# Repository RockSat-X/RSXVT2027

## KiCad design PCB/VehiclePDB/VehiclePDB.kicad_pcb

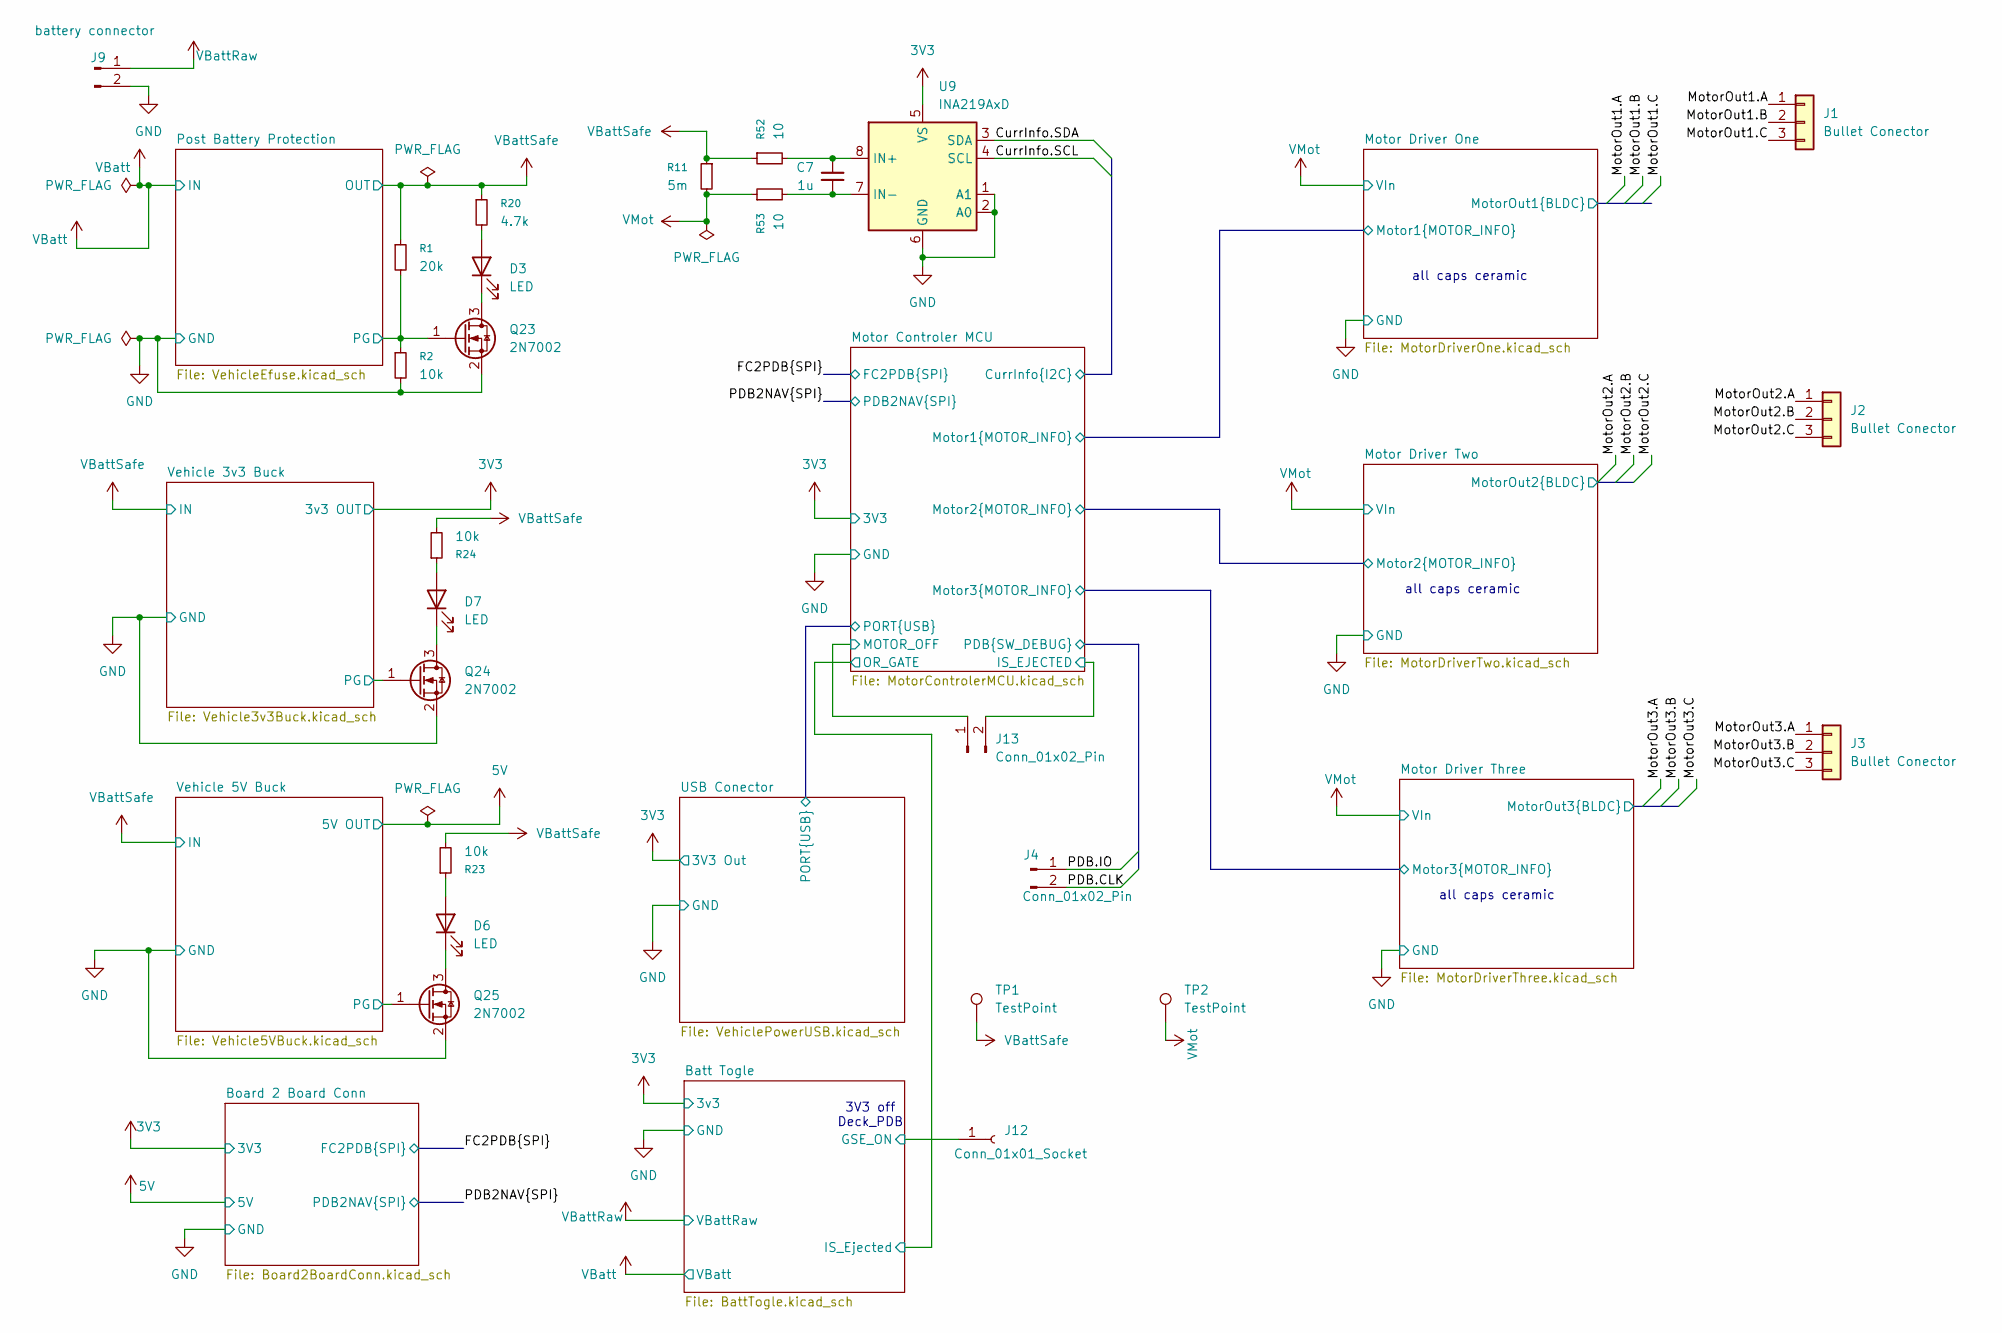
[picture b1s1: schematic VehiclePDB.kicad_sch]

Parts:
C7: 1u; C_0402_1005Metric
D3, D6, D7: LED; LED_0402_1005Metric
J1, J2, J3: Bullet Conector; AMASS_MR30PW-M_1x03_P3.50mm_Horizontal
J4: Conn_01x02_Pin; PinHeader_1x02_P2.54mm_Vertical
J9: battery connector; AMASS_XT30PW-M_1x02_P2.50mm_Horizontal
J12: Conn_01x01_Socket; PinSocket_1x01_P2.00mm_Vertical
J13: Conn_01x02_Pin; JST_PH_B2B-PH-K_1x02_P2.00mm_Vertical
Q23, Q24, Q25: 2N7002; SOT-23
R1: 20k; R_0402_1005Metric
R2, R23, R24: 10k; R_0402_1005Metric
R11: 5m; R_Shunt_Vishay_WSR2_WSR3
R20: 4.7k; R_0402_1005Metric
R52, R53: 10; R_0402_1005Metric
TP1, TP2: TestPoint; TestPoint_Bridge_Pitch2.0mm_Drill0.7mm
U9: INA219AxD; SOIC-8_3.9x4.9mm_P1.27mm

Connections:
3V3: U9.5 (VS); also elsewhere on the board
/Batt Togle/GSE_ON: J12.1 (Pin_1_1); also elsewhere on the board
/Motor Controler MCU/CurrInfo.SCL: U9.4 (SCL); also elsewhere on the board
/Motor Controler MCU/CurrInfo.SDA: U9.3 (SDA); also elsewhere on the board
/Motor Controler MCU/IS_EJECTED: J13.2; also elsewhere on the board
/Motor Controler MCU/MOTOR_OFF: J13.1; also elsewhere on the board
/Motor Controler MCU/PDB.CLK: J4.2; also elsewhere on the board
/Motor Controler MCU/PDB.IO: J4.1; also elsewhere on the board
/Motor Driver One/U.Switch: J1.3; also elsewhere on the board
/Motor Driver One/V.Switch: J1.2; also elsewhere on the board
/Motor Driver One/W.Switch: J1.1; also elsewhere on the board
/Motor Driver Three/U.Switch: J3.3; also elsewhere on the board
/Motor Driver Three/V.Switch: J3.2; also elsewhere on the board
/Motor Driver Three/W.Switch: J3.1; also elsewhere on the board
/Motor Driver Two/U.Switch: J2.3; also elsewhere on the board
/Motor Driver Two/V.Switch: J2.2; also elsewhere on the board
/Motor Driver Two/W.Switch: J2.1; also elsewhere on the board
/Post Battery Protection/PG: Q23.1 (G), R1.2, R2.1; also elsewhere on the board
/Vehicle 3v3 Buck/PG: Q24.1 (G); also elsewhere on the board
/Vehicle 5V Buck/PG: Q25.1 (G); also elsewhere on the board
unnamed: D3.2 (A), R20.2
unnamed: D3.1 (K), Q23.3 (D)
unnamed: D6.2 (A), R23.1
unnamed: D6.1 (K), Q25.3 (D)
unnamed: D7.2 (A), R24.1
unnamed: D7.1 (K), Q24.3 (D)
unnamed: C7.1, R52.2, U9.8 (IN+)
unnamed: C7.2, R53.2, U9.7 (IN-)
VBattRaw: J9.1; also elsewhere on the board
VBattSafe: R1.1, R11.1, R20.1, R23.2, R24.2, R52.1, TP1.1 (1_1); also elsewhere on the board
VMot: R11.2, R53.1, TP2.1 (1_1); also elsewhere on the board

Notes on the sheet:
3V3 off Deck_PDB
all caps ceramic

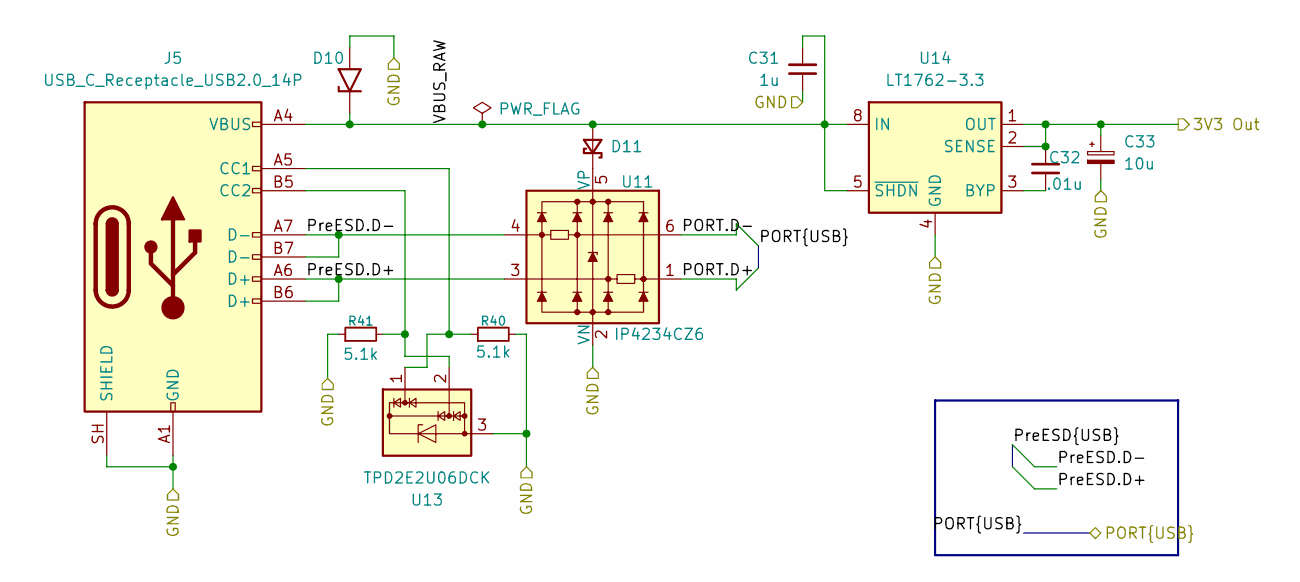
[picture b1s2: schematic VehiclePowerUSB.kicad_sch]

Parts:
C31: 1u; C_0402_1005Metric
C32: .01u; C_0402_1005Metric
C33: 10u; C_0402_1005Metric
D10: SMBJ6.0A-E3/52; D_SMB
D11: BAT54; TSOT-23
J5: USB_C_Receptacle_USB2.0_14P; USB_C_Receptacle_GCT_USB4105-xx-A_16P_TopMnt_Horizontal
R40, R41: 5.1k; R_0402_1005Metric
U11: IP4234CZ6; SC-74-6_1.55x2.9mm_P0.95mm
U13: TPD2E2U06DCK; SOT-323_SC-70
U14: LT1762-3.3; MSOP-8_3x3mm_P0.65mm

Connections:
3V3: C32.1, C33.1, U14.1 (OUT), U14.2 (SENSE); also elsewhere on the board
/USB Conector/PORT.D+: U11.1; also elsewhere on the board
/USB Conector/PORT.D-: U11.6; also elsewhere on the board
/USB Conector/PreESD.D+: J5.A6 (D+), J5.B6 (D+), U11.3
/USB Conector/PreESD.D-: J5.A7 (D-), J5.B7 (D-), U11.4
/USB Conector/VBUS_RAW: C31.1, D10.1 (A1), D11.1 (A), J5.A4 (VBUS), J5.A9 (VBUS), J5.B4 (VBUS), J5.B9 (VBUS), U14.5 (~SHDN), U14.8 (IN)
unnamed: D11.3 (K), U11.5 (VP)
unnamed: J5.A5 (CC1), R40.1, U13.1
unnamed: J5.B5 (CC2), R41.2, U13.2
unnamed: C32.2, U14.3 (BYP)

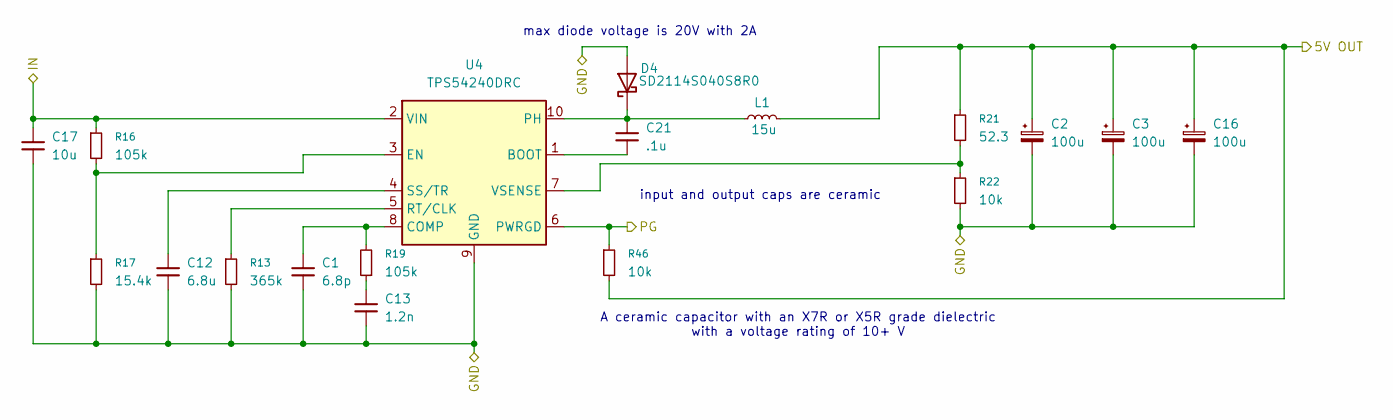
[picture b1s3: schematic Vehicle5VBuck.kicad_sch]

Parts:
C1: 6.8p; C_0402_1005Metric
C2, C3, C16: 100u; C_0402_1005Metric
C12: 6.8u; C_0402_1005Metric
C13: 1.2n; C_0402_1005Metric
C17: 10u; C_0402_1005Metric
C21: .1u; C_0402_1005Metric
D4: SD2114S040S8R0; D_2114_3652Metric
L1: 15u; L_Wurth_WE-LQS-8040
R13: 365k; R_0402_1005Metric
R16, R19: 105k; R_0402_1005Metric
R17: 15.4k; R_0402_1005Metric
R21: 52.3; R_0402_1005Metric
R22, R46: 10k; R_0402_1005Metric
U4: TPS54240DRC; Texas_DRC0010J_ThermalVias

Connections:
5V: C2.1, C3.1, C16.1, L1.2, R21.1, R46.2; also elsewhere on the board
/Vehicle 5V Buck/PG: R46.1, U4.6 (PWRGD); also elsewhere on the board
unnamed: C13.2, R19.1
unnamed: C21.1, D4.1 (K), L1.1, U4.10 (PH)
unnamed: C21.2, U4.1 (BOOT)
unnamed: C1.1, R19.2, U4.8 (COMP)
unnamed: R16.2, R17.1, U4.3 (EN)
unnamed: R13.1, U4.5 (RT/CLK)
unnamed: C12.1, U4.4 (SS/TR)
unnamed: R21.2, R22.1, U4.7 (VSENSE)
VBattSafe: C17.1, R16.1, U4.2 (VIN); also elsewhere on the board

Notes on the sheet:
A ceramic capacitor with an X7R or X5R grade dielectric with a voltage rating of 10+ V
input and output caps are ceramic
max diode voltage is 20V with 2A

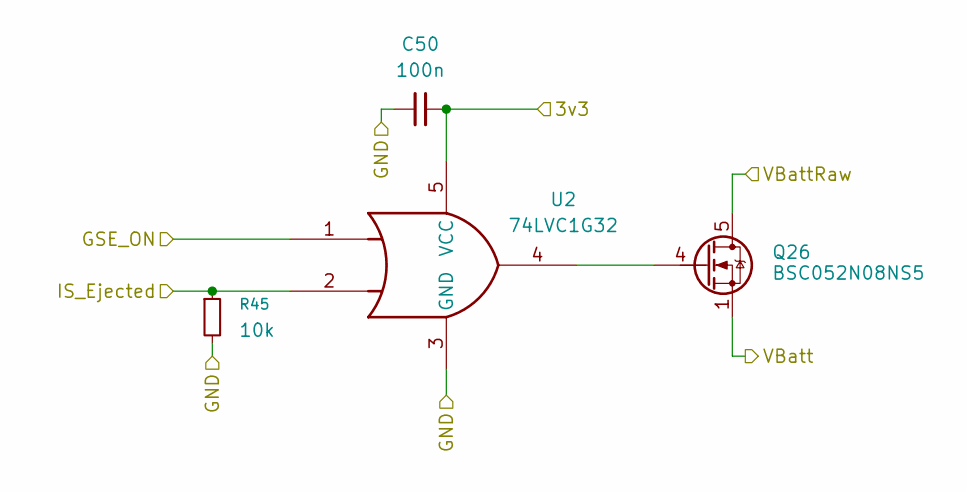
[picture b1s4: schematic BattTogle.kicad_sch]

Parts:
C50: 100n; C_0402_1005Metric
Q26: BSC052N08NS5; TDSON-8-1
R45: 10k; R_0402_1005Metric_Pad0.72x0.64mm_HandSolder
U2: 74LVC1G32; SOT-23-5

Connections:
3V3: C50.2, U2.5 (VCC); also elsewhere on the board
/Batt Togle/GSE_ON: U2.1; also elsewhere on the board
unnamed: Q26.4 (G), U2.4
VBatt: Q26.1 (S), Q26.2 (S), Q26.3 (S); also elsewhere on the board
VBattRaw: Q26.5 (D); also elsewhere on the board

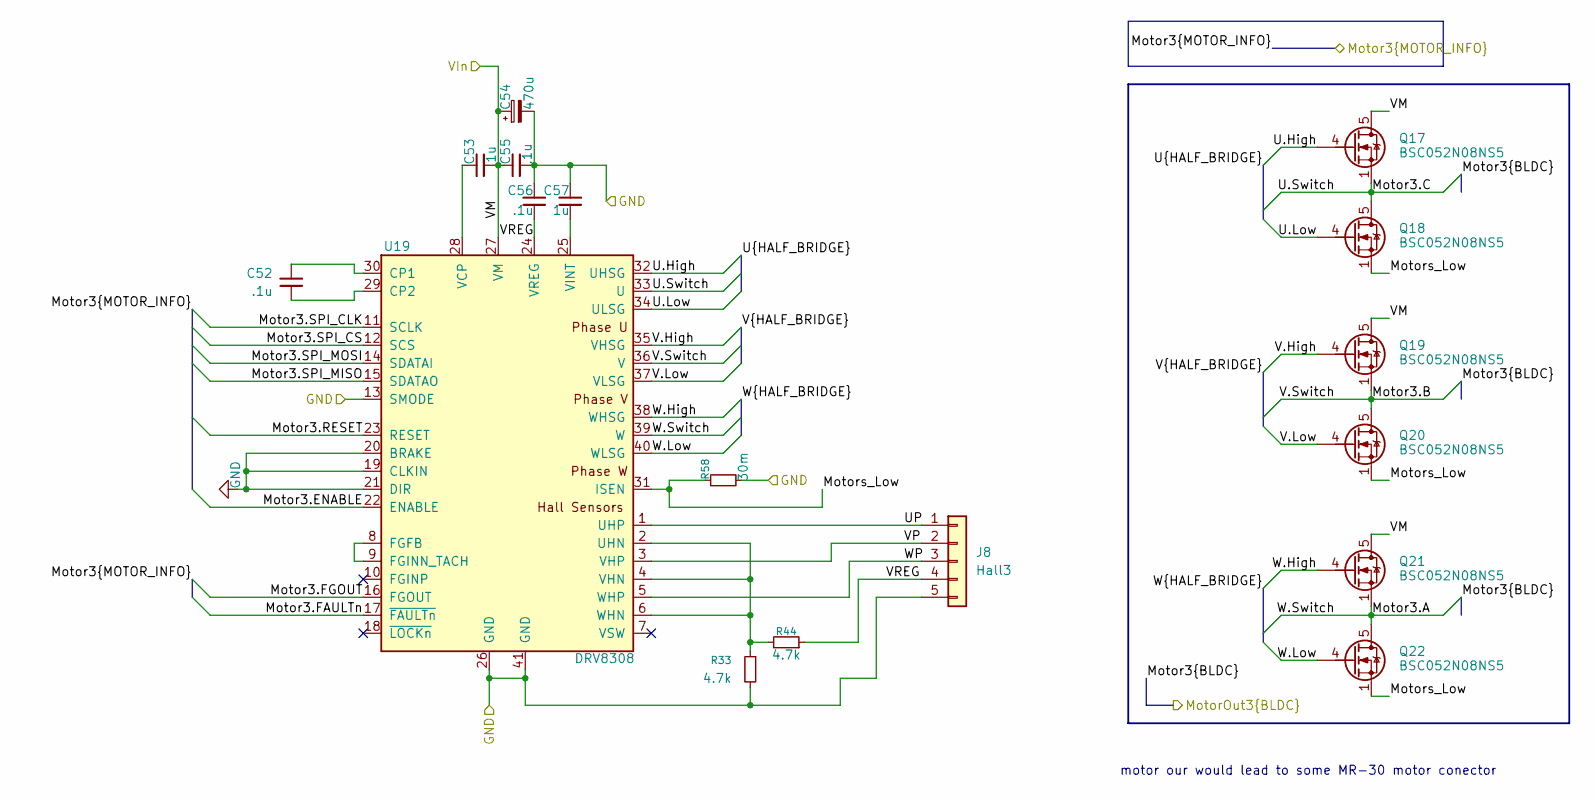
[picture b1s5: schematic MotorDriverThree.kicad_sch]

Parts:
C52, C55, C56: .1u; C_0402_1005Metric
C53, C57: 1u; C_0402_1005Metric
C54: 470u; C_0402_1005Metric
J8: Hall3; JST_GH_SM05B-GHS-TB_1x05-1MP_P1.25mm_Horizontal
Q17, Q18, Q19, Q20, Q21, Q22: BSC052N08NS5; TDSON-8-1
R33, R44: 4.7k; R_0402_1005Metric
R58: 30m; R_Shunt_Vishay_WSR2_WSR3
U19: DRV8308; Texas_RHA0040E_VQFN-40-1EP_6x6mm_P0.5mm_EP3.52x2.62mm

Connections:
/Motor Driver Three/Motor3.ENABLE: U19.22 (ENABLE); also elsewhere on the board
/Motor Driver Three/Motor3.FAULTn: U19.17 (~FAULTn); also elsewhere on the board
/Motor Driver Three/Motor3.FGOUT: U19.16 (FGOUT); also elsewhere on the board
/Motor Driver Three/Motor3.RESET: U19.23 (RESET); also elsewhere on the board
/Motor Driver Three/Motor3.SPI_CLK: U19.11 (SCLK); also elsewhere on the board
/Motor Driver Three/Motor3.SPI_CS: U19.12 (SCS); also elsewhere on the board
/Motor Driver Three/Motor3.SPI_MISO: U19.15 (SDATAO); also elsewhere on the board
/Motor Driver Three/Motor3.SPI_MOSI: U19.14 (SDATAI); also elsewhere on the board
/Motor Driver Three/Motors_Low: Q18.1 (S), Q18.2 (S), Q18.3 (S), Q20.1 (S), Q20.2 (S), Q20.3 (S), Q22.1 (S), Q22.2 (S), Q22.3 (S), R58.1, U19.31 (ISEN)
/Motor Driver Three/U.High: Q17.4 (G), U19.32 (UHSG)
/Motor Driver Three/U.Low: Q18.4 (G), U19.34 (ULSG)
/Motor Driver Three/U.Switch: Q17.1 (S), Q17.2 (S), Q17.3 (S), Q18.5 (D), U19.33 (U); also elsewhere on the board
/Motor Driver Three/UP: J8.1, U19.1 (UHP)
/Motor Driver Three/V.High: Q19.4 (G), U19.35 (VHSG)
/Motor Driver Three/V.Low: Q20.4 (G), U19.37 (VLSG)
/Motor Driver Three/V.Switch: Q19.1 (S), Q19.2 (S), Q19.3 (S), Q20.5 (D), U19.36 (V); also elsewhere on the board
/Motor Driver Three/VP: J8.2, U19.3 (VHP)
/Motor Driver Three/W.High: Q21.4 (G), U19.38 (WHSG)
/Motor Driver Three/W.Low: Q22.4 (G), U19.40 (WLSG)
/Motor Driver Three/W.Switch: Q21.1 (S), Q21.2 (S), Q21.3 (S), Q22.5 (D), U19.39 (W); also elsewhere on the board
/Motor Driver Three/WP: J8.3, U19.5 (WHP)
unnamed: C52.1, U19.30 (CP1)
unnamed: C52.2, U19.29 (CP2)
unnamed: U19.8 (FGFB), U19.9 (FGINN_TACH)
unnamed: C53.1, U19.28 (VCP)
unnamed: C57.2, U19.25 (VINT)
VMot: C53.2, C54.1, C55.1, Q17.5 (D), Q19.5 (D), Q21.5 (D), U19.27 (VM); also elsewhere on the board

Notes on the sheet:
motor our would lead to some MR-30 motor conector

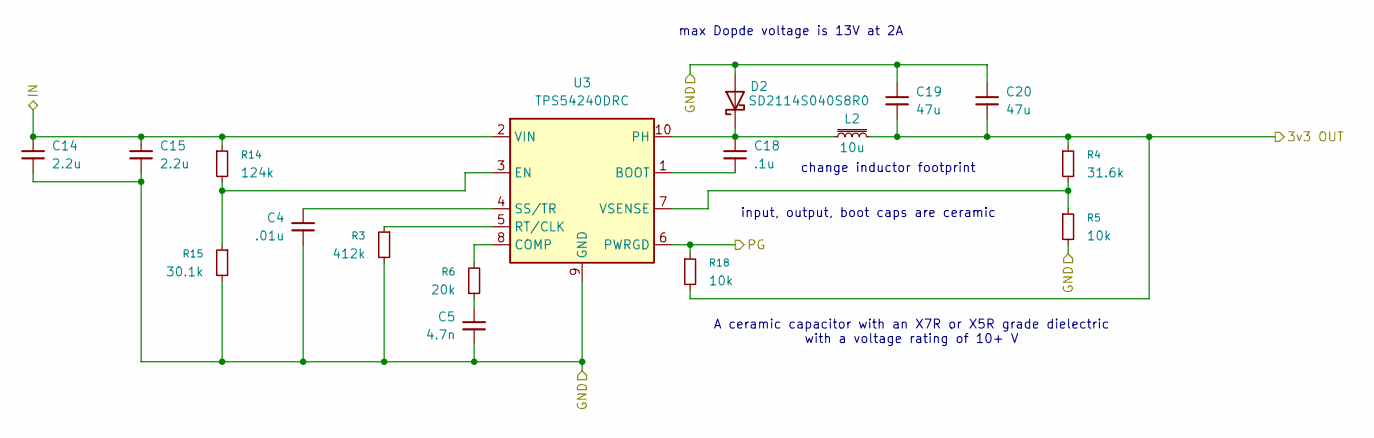
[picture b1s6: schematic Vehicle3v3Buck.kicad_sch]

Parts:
C4: .01u; C_0402_1005Metric
C5: 4.7n; C_0402_1005Metric
C14, C15: 2.2u; C_0402_1005Metric
C18: .1u; C_0402_1005Metric
C19, C20: 47u; C_0402_1005Metric
D2: SD2114S040S8R0; D_2114_3652Metric
L2: 10u; L_Wurth_WE-LQS-8040
R3: 412k; R_0402_1005Metric
R4: 31.6k; R_0402_1005Metric
R5, R18: 10k; R_0402_1005Metric
R6: 20k; R_0402_1005Metric
R14: 124k; R_0402_1005Metric
R15: 30.1k; R_0402_1005Metric
U3: TPS54240DRC; Texas_DRC0010J_ThermalVias

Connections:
3V3: C19.2, C20.2, L2.2, R4.1, R18.2; also elsewhere on the board
/Vehicle 3v3 Buck/PG: R18.1, U3.6 (PWRGD); also elsewhere on the board
unnamed: C5.2, R6.1
unnamed: C18.1, D2.1 (K), L2.1, U3.10 (PH)
unnamed: C18.2, U3.1 (BOOT)
unnamed: R6.2, U3.8 (COMP)
unnamed: R14.2, R15.1, U3.3 (EN)
unnamed: R3.1, U3.5 (RT/CLK)
unnamed: C4.1, U3.4 (SS/TR)
unnamed: R4.2, R5.1, U3.7 (VSENSE)
VBattSafe: C14.1, C15.1, R14.1, U3.2 (VIN); also elsewhere on the board

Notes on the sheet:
input, output, boot caps are ceramic
change inductor footprint
A ceramic capacitor with an X7R or X5R grade dielectric with a voltage rating of 10+ V
max Dopde voltage is 13V at 2A

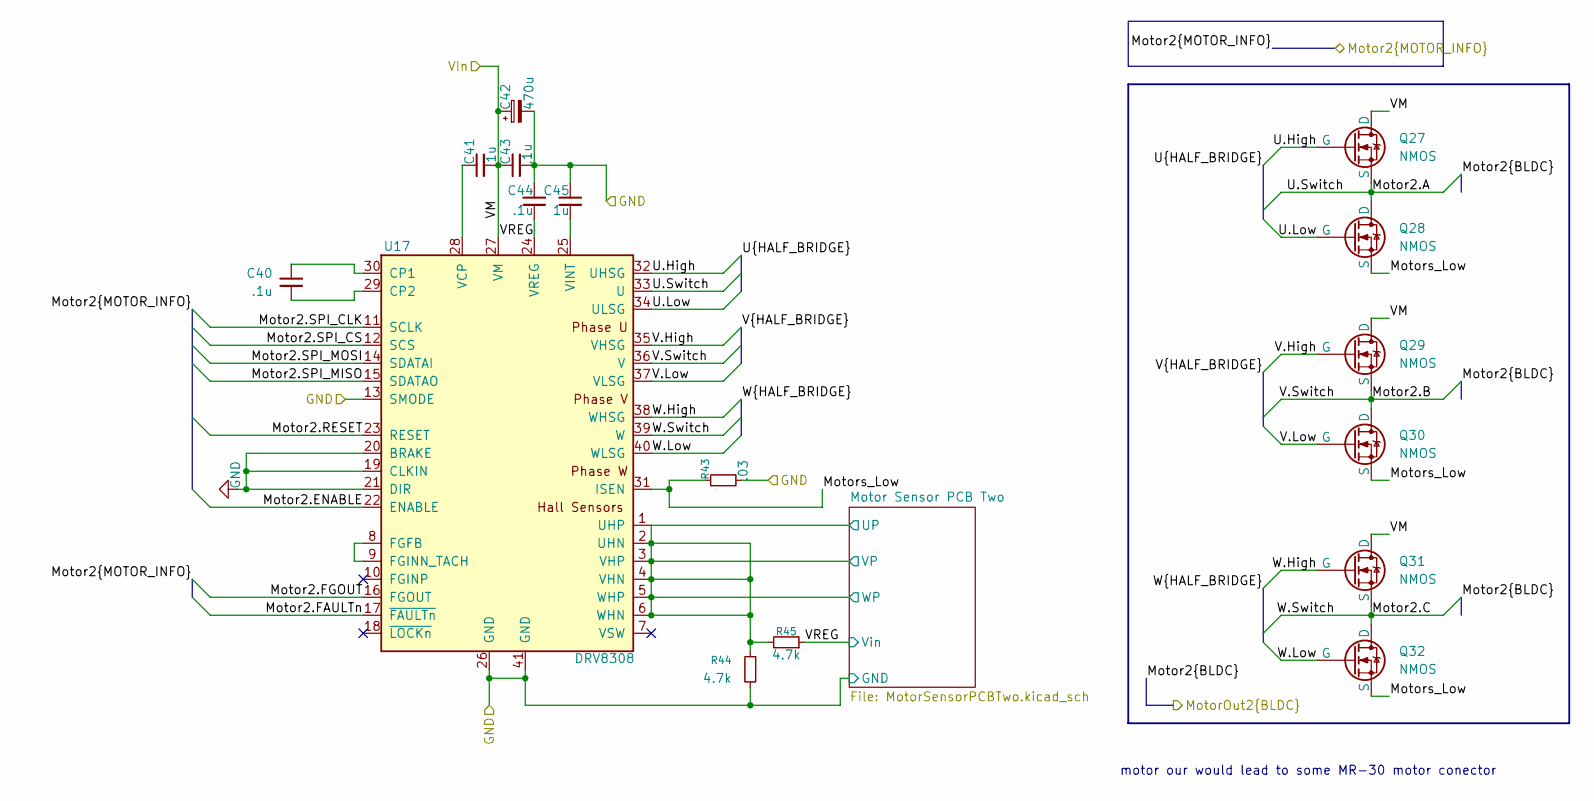
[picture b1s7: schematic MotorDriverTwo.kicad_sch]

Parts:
C40, C43, C44: .1u; C_0402_1005Metric
C41, C45: 1u; C_0402_1005Metric
C42: 470u; C_0402_1005Metric
Q27, Q28, Q29, Q30, Q31, Q32: NMOS
R43: .03; R_0402_1005Metric
R44, R45: 4.7k; R_0402_1005Metric
U17: DRV8308; Texas_RHA0040E_VQFN-40-1EP_6x6mm_P0.5mm_EP3.52x2.62mm

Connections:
/Motor Driver Three/Motor3.RESET: U17.23 (RESET); also elsewhere on the board
/Motor Driver Three/Motor3.SPI_CLK: U17.11 (SCLK); also elsewhere on the board
/Motor Driver Three/Motor3.SPI_MISO: U17.15 (SDATAO); also elsewhere on the board
/Motor Driver Three/Motor3.SPI_MOSI: U17.14 (SDATAI); also elsewhere on the board
/Motor Driver Two/Motor2.ENABLE: U17.22 (ENABLE); also elsewhere on the board
/Motor Driver Two/Motor2.FAULTn: U17.17 (~FAULTn); also elsewhere on the board
/Motor Driver Two/Motor2.FGOUT: U17.16 (FGOUT); also elsewhere on the board
/Motor Driver Two/Motor2.SPI_CS: U17.12 (SCS); also elsewhere on the board
/Motor Driver Two/Motors_Low: Q28.3 (S), Q30.3 (S), Q32.3 (S), R43.1, U17.31 (ISEN); also elsewhere on the board
/Motor Driver Two/U.High: Q27.2 (G), U17.32 (UHSG); also elsewhere on the board
/Motor Driver Two/U.Low: Q28.2 (G), U17.34 (ULSG); also elsewhere on the board
/Motor Driver Two/U.Switch: Q27.3 (S), Q28.1 (D), U17.33 (U); also elsewhere on the board
/Motor Driver Two/V.High: Q29.2 (G), U17.35 (VHSG); also elsewhere on the board
/Motor Driver Two/V.Low: Q30.2 (G), U17.37 (VLSG); also elsewhere on the board
/Motor Driver Two/V.Switch: Q29.3 (S), Q30.1 (D), U17.36 (V); also elsewhere on the board
/Motor Driver Two/W.High: Q31.2 (G), U17.38 (WHSG); also elsewhere on the board
/Motor Driver Two/W.Low: Q32.2 (G), U17.40 (WLSG); also elsewhere on the board
/Motor Driver Two/W.Switch: Q31.3 (S), Q32.1 (D), U17.39 (W); also elsewhere on the board
unnamed: C40.1, U17.30 (CP1)
unnamed: C40.2, U17.29 (CP2)
unnamed: U17.8 (FGFB), U17.9 (FGINN_TACH)
unnamed: C41.1, U17.28 (VCP)
unnamed: C45.2, U17.25 (VINT)
VMot: C41.2, C42.1, C43.1, Q27.1 (D), Q29.1 (D), Q31.1 (D), U17.27 (VM); also elsewhere on the board

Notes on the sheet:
motor our would lead to some MR-30 motor conector

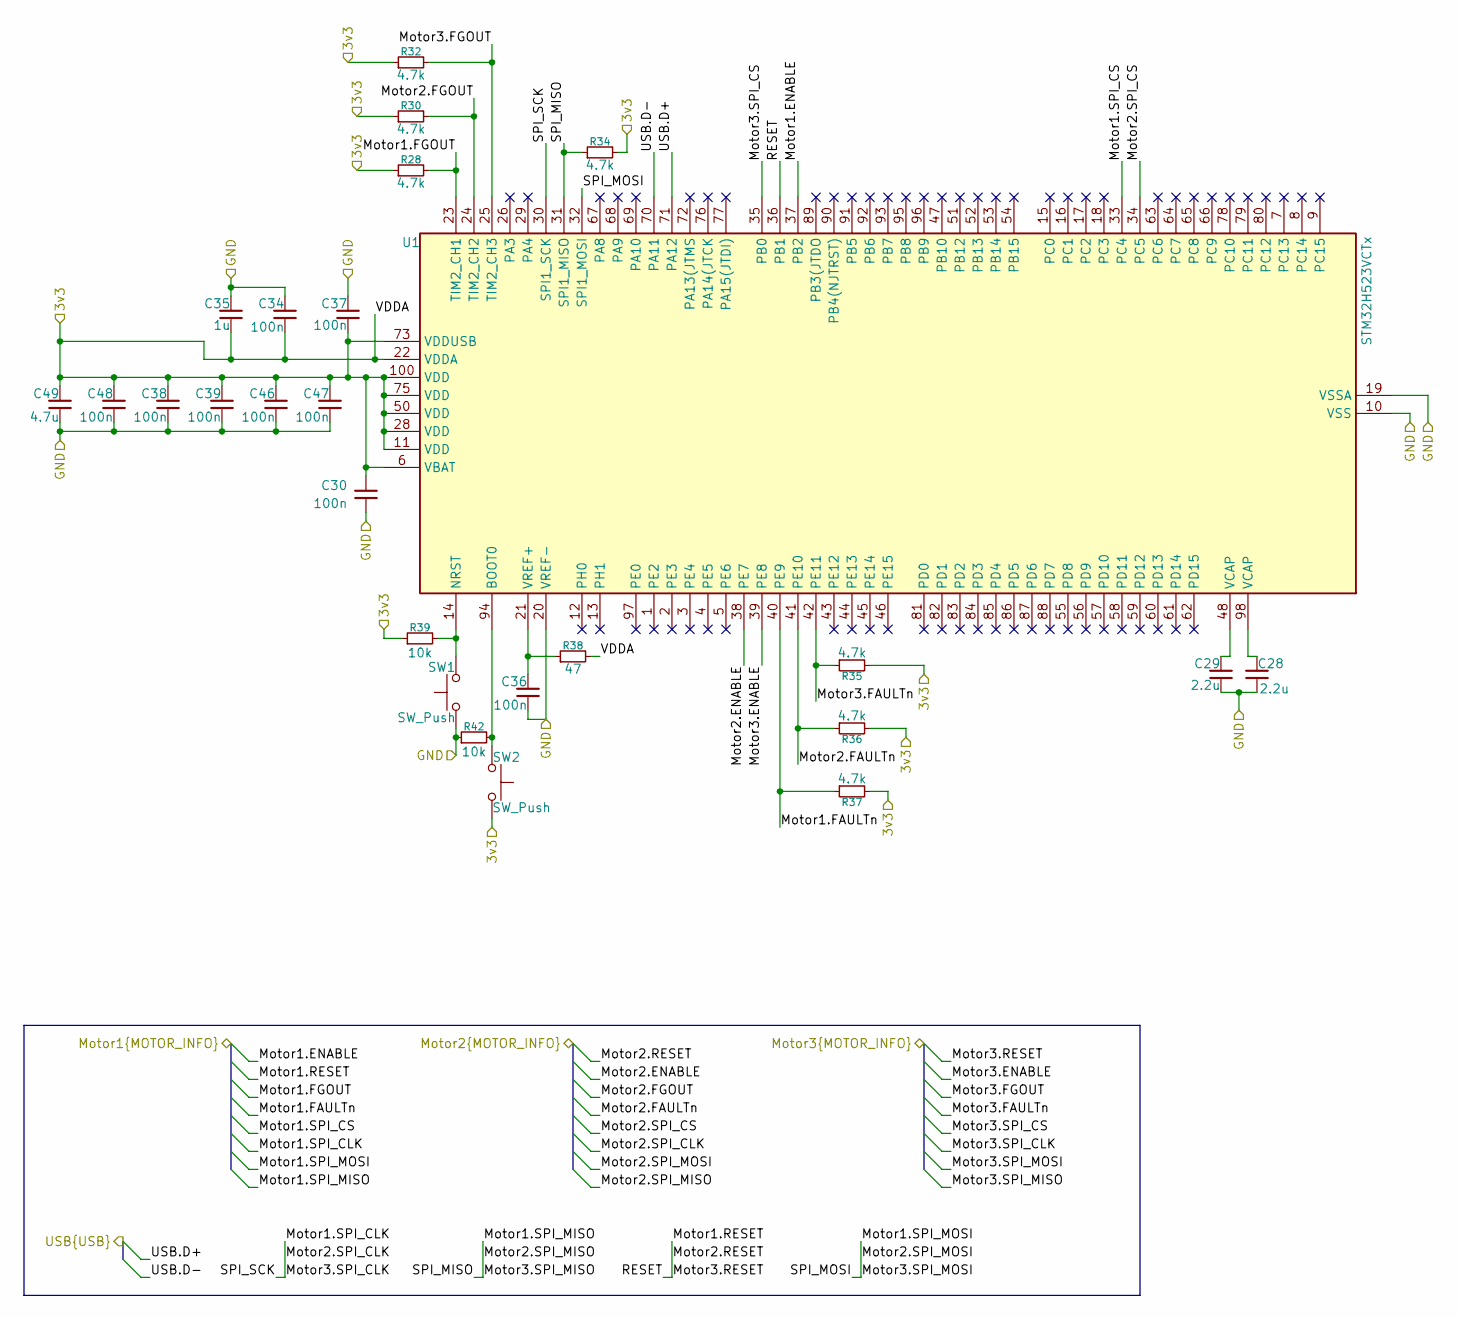
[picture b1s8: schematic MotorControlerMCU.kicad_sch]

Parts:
C28, C29: 2.2u; C_0402_1005Metric
C30, C34, C36, C37, C38, C39, C46, C47, C48: 100n; C_0402_1005Metric
C35: 1u; C_0402_1005Metric
C49: 4.7u; C_0402_1005Metric
R28, R30, R32, R34, R35, R36, R37: 4.7k; R_0402_1005Metric
R38: 47; R_0402_1005Metric
R39, R42: 10k; R_0402_1005Metric
SW1, SW2: SW_Push; SW_Push_1P1T_NO_CK_KMR2
U1: STM32H523VCTx; LQFP-100_14x14mm_P0.5mm

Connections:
3V3: C30.1, C34.2, C35.2, C37.1, C38.1, C39.1, C46.1, C47.1, C48.1, C49.1, R28.1, R30.1, R32.1, R34.2, R35.2, R36.2, R37.2, R38.2, R39.1, SW2.1, U1.6 (VBAT), U1.11 (VDD), U1.22 (VDDA), U1.28 (VDD), U1.50 (VDD), U1.73 (VDDUSB), U1.75 (VDD), U1.100 (VDD); also elsewhere on the board
/FC2PDB.CLK: U1.47 (SPI2_SCK); also elsewhere on the board
/FC2PDB.CS: U1.15 (PC0); also elsewhere on the board
/FC2PDB.MISO: U1.17 (SPI2_MISO); also elsewhere on the board
/FC2PDB.MOSI: U1.16 (SPI2_MOSI); also elsewhere on the board
/Motor Controler MCU/CurrInfo.SCL: U1.92 (I2C1_SCL); also elsewhere on the board
/Motor Controler MCU/CurrInfo.SDA: U1.93 (I2C1_SDA); also elsewhere on the board
/Motor Controler MCU/IS_EJECTED: U1.96 (PB9); also elsewhere on the board
/Motor Controler MCU/MOTOR_OFF: U1.97 (PE0); also elsewhere on the board
/Motor Controler MCU/PDB.CLK: U1.76 (DEBUG_JTCK-SWCLK); also elsewhere on the board
/Motor Controler MCU/PDB.IO: U1.72 (DEBUG_JTMS-SWDIO); also elsewhere on the board
/Motor Driver One/Motor1.ENABLE: U1.37 (PB2); also elsewhere on the board
/Motor Driver One/Motor1.FAULTn: R37.1, U1.40 (PE9); also elsewhere on the board
/Motor Driver One/Motor1.FGOUT: R28.2, U1.23 (TIM2_CH1); also elsewhere on the board
/Motor Driver One/Motor1.SPI_CS: U1.33 (PC4); also elsewhere on the board
/Motor Driver Three/Motor3.ENABLE: U1.39 (PE8); also elsewhere on the board
/Motor Driver Three/Motor3.FAULTn: R35.1, U1.42 (PE11); also elsewhere on the board
/Motor Driver Three/Motor3.FGOUT: R32.2, U1.25 (TIM2_CH3); also elsewhere on the board
/Motor Driver Three/Motor3.RESET: U1.36 (PB1); also elsewhere on the board
/Motor Driver Three/Motor3.SPI_CLK: U1.30 (SPI1_SCK); also elsewhere on the board
/Motor Driver Three/Motor3.SPI_CS: U1.35 (PB0); also elsewhere on the board
/Motor Driver Three/Motor3.SPI_MISO: R34.1, U1.31 (SPI1_MISO); also elsewhere on the board
/Motor Driver Three/Motor3.SPI_MOSI: U1.32 (SPI1_MOSI); also elsewhere on the board
/Motor Driver Two/Motor2.ENABLE: U1.38 (PE7); also elsewhere on the board
/Motor Driver Two/Motor2.FAULTn: R36.1, U1.41 (PE10); also elsewhere on the board
/Motor Driver Two/Motor2.FGOUT: R30.2, U1.24 (TIM2_CH2); also elsewhere on the board
/Motor Driver Two/Motor2.SPI_CS: U1.34 (PC5); also elsewhere on the board
/PDB2NAV.CLK: U1.1 (SPI4_SCK); also elsewhere on the board
/PDB2NAV.CS: U1.3 (PE4); also elsewhere on the board
/PDB2NAV.MISO: U1.4 (SPI4_MISO); also elsewhere on the board
/PDB2NAV.MOSI: U1.5 (SPI4_MOSI); also elsewhere on the board
/USB Conector/PORT.D+: U1.71 (USB_DP); also elsewhere on the board
/USB Conector/PORT.D-: U1.70 (USB_DM); also elsewhere on the board
unnamed: C28.1, U1.98 (VCAP)
unnamed: C29.1, U1.48 (VCAP)
unnamed: R42.2, SW2.2, U1.94 (BOOT0)
unnamed: R39.2, SW1.2, U1.14 (NRST)
unnamed: C36.1, R38.1, U1.21 (VREF+)

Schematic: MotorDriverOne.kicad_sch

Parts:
C22, C24, C26: .1u; C_0402_1005Metric
C23, C25: 1u; C_0402_1005Metric
C27: 470u; C_0402_1005Metric
J6: Hall1; JST_GH_SM05B-GHS-TB_1x05-1MP_P1.25mm_Horizontal
Q1, Q6, Q7, Q8, Q9, Q10: BSC052N08NS5; TDSON-8-1
R25: 30m; R_Shunt_Vishay_WSR2_WSR3
R26, R27: 4.7k; R_0402_1005Metric
U5: DRV8308; Texas_RHA0040E_VQFN-40-1EP_6x6mm_P0.5mm_EP3.52x2.62mm

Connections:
/Motor Driver One/Motor1.ENABLE: U5.22 (ENABLE); also elsewhere on the board
/Motor Driver One/Motor1.FAULTn: U5.17 (~FAULTn); also elsewhere on the board
/Motor Driver One/Motor1.FGOUT: U5.16 (FGOUT); also elsewhere on the board
/Motor Driver One/Motor1.SPI_CS: U5.12 (SCS); also elsewhere on the board
/Motor Driver One/Motors_Low: Q6.1 (S), Q6.2 (S), Q6.3 (S), Q7.1 (S), Q7.2 (S), Q7.3 (S), Q9.1 (S), Q9.2 (S), Q9.3 (S), R25.1, U5.31 (ISEN)
/Motor Driver One/U.High: Q1.4 (G), U5.32 (UHSG)
/Motor Driver One/U.Low: Q6.4 (G), U5.34 (ULSG)
/Motor Driver One/U.Switch: Q1.1 (S), Q1.2 (S), Q1.3 (S), Q6.5 (D), U5.33 (U); also elsewhere on the board
/Motor Driver One/UP: J6.1, U5.1 (UHP)
/Motor Driver One/V.High: Q8.4 (G), U5.35 (VHSG)
/Motor Driver One/V.Low: Q7.4 (G), U5.37 (VLSG)
/Motor Driver One/V.Switch: Q7.5 (D), Q8.1 (S), Q8.2 (S), Q8.3 (S), U5.36 (V); also elsewhere on the board
/Motor Driver One/VP: J6.2, U5.3 (VHP)
/Motor Driver One/VREG: C24.2, J6.4, R26.1, U5.24 (VREG)
/Motor Driver One/W.High: Q10.4 (G), U5.38 (WHSG)
/Motor Driver One/W.Low: Q9.4 (G), U5.40 (WLSG)
/Motor Driver One/W.Switch: Q9.5 (D), Q10.1 (S), Q10.2 (S), Q10.3 (S), U5.39 (W); also elsewhere on the board
/Motor Driver One/WP: J6.3, U5.5 (WHP)
/Motor Driver Three/Motor3.RESET: U5.23 (RESET); also elsewhere on the board
/Motor Driver Three/Motor3.SPI_CLK: U5.11 (SCLK); also elsewhere on the board
/Motor Driver Three/Motor3.SPI_MISO: U5.15 (SDATAO); also elsewhere on the board
/Motor Driver Three/Motor3.SPI_MOSI: U5.14 (SDATAI); also elsewhere on the board
unnamed: C22.1, U5.30 (CP1)
unnamed: C22.2, U5.29 (CP2)
unnamed: U5.8 (FGFB), U5.9 (FGINN_TACH)
unnamed: R26.2, R27.1, U5.2 (UHN), U5.4 (VHN), U5.6 (WHN)
unnamed: C23.1, U5.28 (VCP)
unnamed: C25.2, U5.25 (VINT)
VMot: C23.2, C26.1, C27.1, Q1.5 (D), Q8.5 (D), Q10.5 (D), U5.27 (VM); also elsewhere on the board

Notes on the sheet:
motor our would lead to some MR-30 motor conector

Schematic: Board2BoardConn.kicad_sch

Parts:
J10, J11: Conn_02x06_Odd_Even; JST_PHD_B12B-PHDSS_2x06_P2.00mm_Vertical

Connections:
3V3: J10.7, J10.8, J11.7, J11.8; also elsewhere on the board
5V: J10.9, J10.10, J11.9, J11.10; also elsewhere on the board
/FC2PDB.CLK: J10.4; also elsewhere on the board
/FC2PDB.CS: J10.1; also elsewhere on the board
/FC2PDB.MISO: J10.2; also elsewhere on the board
/FC2PDB.MOSI: J10.3; also elsewhere on the board
/PDB2NAV.CLK: J11.4; also elsewhere on the board
/PDB2NAV.CS: J11.1; also elsewhere on the board
/PDB2NAV.MISO: J11.2; also elsewhere on the board
/PDB2NAV.MOSI: J11.3; also elsewhere on the board

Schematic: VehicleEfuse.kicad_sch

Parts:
C6: .01u; C_0402_1005Metric
C8: 2.2n; C_0402_1005Metric
C9: 4.3n; C_0402_1005Metric
C10: 8.2n; C_0402_1005Metric
C11: 400u; C_0402_1005Metric
D1: SD2114S040S8R0; D_2114_3652Metric
D5: SMF15A; D_SMF
Q5: BSC026N08NS5; TDSON-8-1
R7: 500k; R_0402_1005Metric
R8: 14k; R_0402_1005Metric
R9: 50k; R_0402_1005Metric
R10: 226; R_0402_1005Metric
R12: 1.24k; R_0402_1005Metric
R47: 2; R_0402_1005Metric
U6: TPS25983

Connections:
/Post Battery Protection/PG: U6.13 (PG); also elsewhere on the board
unnamed: Q5.4 (G), R47.1
unnamed: Q5.1 (S), Q5.2 (S), Q5.3 (S), U6.17 (OUT), U6.18 (OUT), U6.19 (OUT), U6.20 (OUT), U6.21 (OUT), U6.22 (OUT), U6.23 (OUT), U6.24 (OUT)
unnamed: R7.1, R8.2, U6.6 (EN/UVLO)
unnamed: R10.1, U6.8 (ILIM)
unnamed: R12.1, U6.9 (IMON)
unnamed: C9.1, U6.7 (ITIMER)
unnamed: R8.1, R9.2, U6.12 (OVLO)
unnamed: C8.2, U6.10 (RETRY_DEL)
unnamed: C10.1, R47.2, U6.15 (dVdt)
VBatt: C6.1, D5.1 (A1), R7.2, U6.1 (IN), U6.2 (IN), U6.3 (IN), U6.16 (IN), U6.25 (IN); also elsewhere on the board
VBattSafe: C11.1, D1.1 (K), Q5.5 (D); also elsewhere on the board

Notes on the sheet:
Cout is a cermaic cap
short NRETRY for inf retrys
Cin is a cermaic cap

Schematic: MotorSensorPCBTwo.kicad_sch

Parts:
C61, C62, C63: 10n
R49, R50, R51: 4.7k; R_0402_1005Metric
U21, U22, U23: TMAG5110C2xxDBV; SOT-23-5

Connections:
unnamed: C61.1, C62.1, C63.1, U21.2 (GND), U21.3 (NC), U22.2 (GND), U22.3 (NC), U23.2 (GND), U23.3 (NC)
unnamed: C61.2, C62.2, C63.2, R49.1, R50.1, R51.1, U21.1 (VCC), U22.1 (VCC), U23.1 (VCC)
unnamed: R49.2, U21.4 (OUT1)
unnamed: R50.2, U22.4 (OUT1)
unnamed: R51.2, U23.4 (OUT1)

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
